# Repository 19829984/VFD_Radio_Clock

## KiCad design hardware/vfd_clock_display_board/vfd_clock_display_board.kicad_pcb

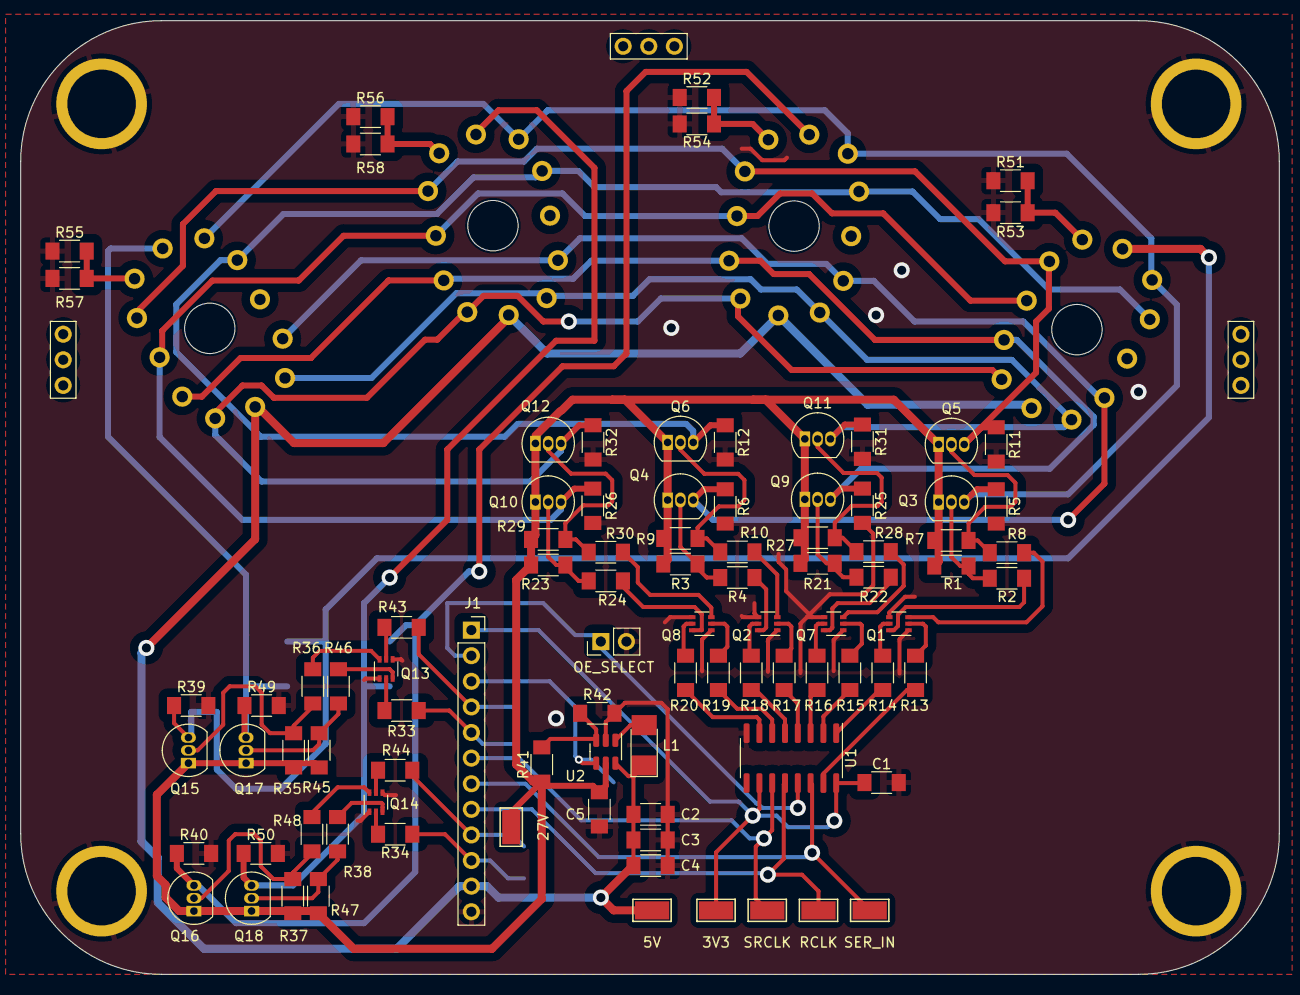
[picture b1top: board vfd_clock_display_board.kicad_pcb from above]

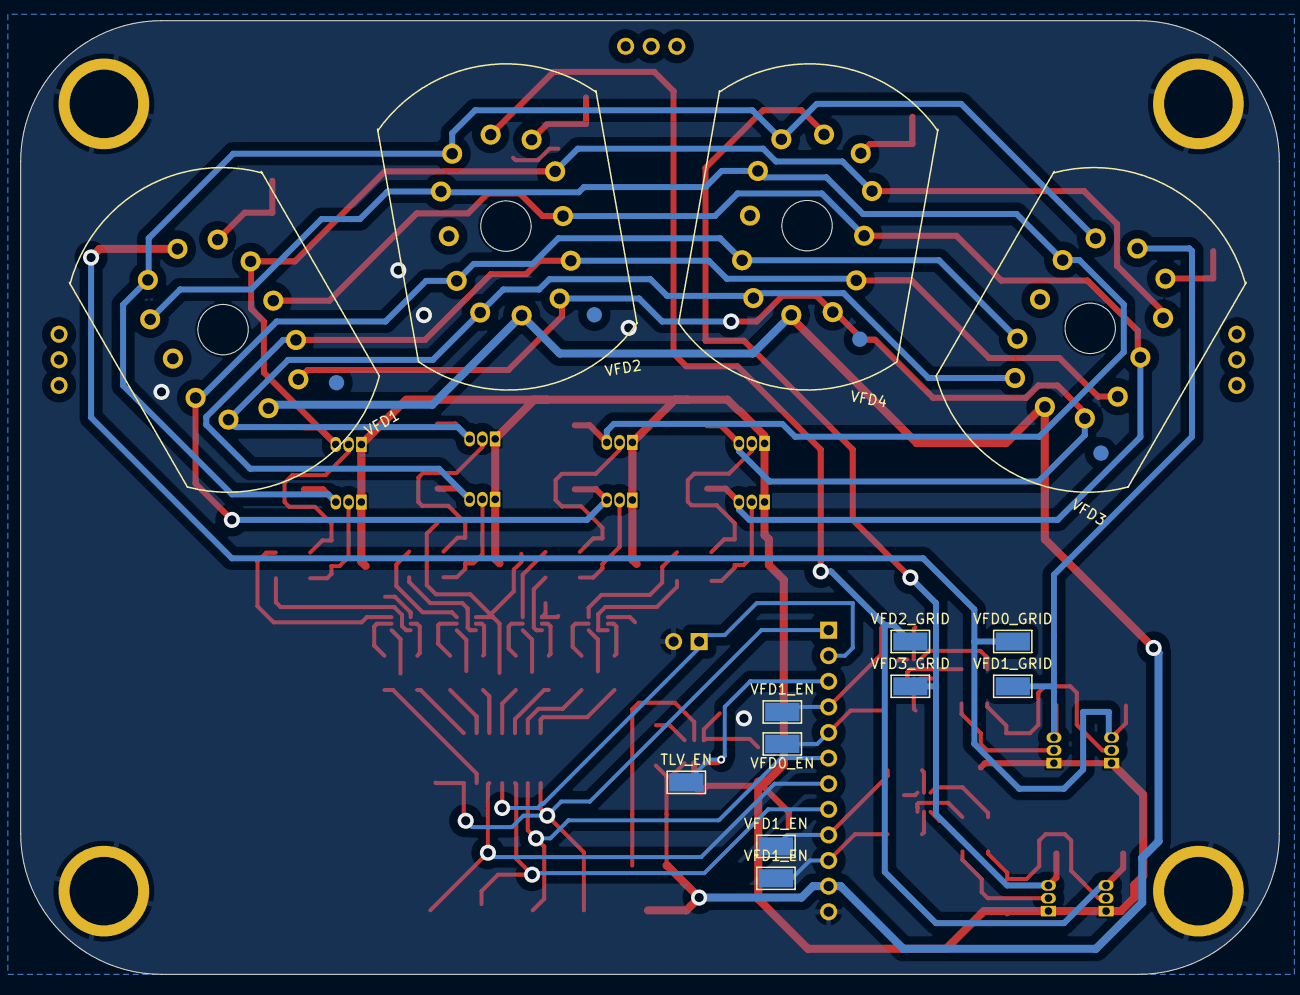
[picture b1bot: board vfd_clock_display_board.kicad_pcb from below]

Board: 2 copper layers, 124.9 x 94.6 mm, 105 parts (13 on the bottom side), 75 nets.

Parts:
3V3, 5V, 27V: TestPoint_Keystone_5015_Micro-Minature
C1, C2, C3, C4: 1uF; C_1206
C5: 10uF; C_1206
J1: Conn_01x12_Pin; PinSocket_1x12_P2.54mm_Vertical
L1: 22uH; L_1210
OE_SELECT: Conn_01x02_Pin; PinHeader_1x02_P2.54mm_Vertical
Q1, Q2, Q7, Q8, Q13, Q14: MMDT5551; SOT-363_SC-70-6
Q3, Q4, Q5, Q6, Q9, Q10, Q11, Q12, Q15, Q16, Q17, Q18: 2N3906; TO-92_Inline
R1, R3, R7, R9, R21, R23, R27, R29, R35, R37, R45, R47: R_220K; R_1206
R2, R4, R8, R10, R22, R24, R28, R30, R36, R38, R46, R48: R_50K; R_1206
R5, R6, R11, R12, R25, R26, R31, R32, R39, R40, R49, R50: R_100K; R_1206
R13, R14, R15, R16, R17, R18, R19, R20, R33, R34, R43, R44: R_22K; R_1206
R41: 2.37M; R_1206
R42: 71.5K; R_1206
R51, R52, R53, R54, R55, R56, R57, R58: 75; R_1206
RCLK: TestPoint_Keystone_5015_Micro-Minature
SER_IN: TestPoint_Keystone_5015_Micro-Minature
SRCLK: TestPoint_Keystone_5015_Micro-Minature
TLV_EN: TestPoint_Keystone_5015_Micro-Minature
U1: 74HC595; SOIC-16_3.9x9.9mm_P1.27mm
U2: TLV61046ADB; SOT-23-6
VFD0_EN, VFD0_GRID, VFD1_EN, VFD1_EN#2, VFD1_EN#3, VFD1_GRID, VFD2_GRID, VFD3_GRID: TestPoint_Keystone_5015_Micro-Minature
VFD1, VFD2, VFD3, VFD4: IV-22

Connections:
27V: 27V.1, C5.1, Q3.1 (E), Q4.1 (E), Q5.1 (E), Q6.1 (E), Q9.1 (E), Q10.1 (E), Q11.1 (E), Q12.1 (E), Q15.1 (E), Q16.1 (E), Q17.1 (E), Q18.1 (E), R1.1, R3.1, R7.1, R9.1, R21.1, R23.1, R27.1, R29.1, R35.1, R37.1, R41.1, R45.1, R47.1, U2.5 (VOUT)
/0QA: Q1.2 (B1), R13.1
/0QB: Q1.5 (B2), R14.1
/0QC: Q7.2 (B1), R15.2
/0QD: Q7.5 (B2), R16.2
/0QE: Q2.2 (B1), R17.2
/0QF: Q2.5 (B2), R18.1
/0QG: Q8.2 (B1), R19.1
/0QH: Q8.5 (B2), R20.1
/OE: J1.2, OE_SELECT.1, U1.13 (~OE)
/RCLK: J1.8, RCLK.1, U1.12 (RCLK)
/SER_IN: J1.7, SER_IN.1, U1.14 (SER)
/SRCLK: J1.6, SRCLK.1, U1.11 (SRCLK)
/TLV_EN: J1.3, TLV_EN.1, U2.4 (EN)
/VFD0_EN: J1.5, R33.2, VFD0_EN.1
/VFD0_GRID: Q15.3 (C), R39.1, VFD0_GRID.1, VFD1.6 (Grid)
/VFD1_EN: J1.4, R43.1, VFD1_EN.1
/VFD1_GRID: Q17.3 (C), R49.1, VFD1_GRID.1, VFD3.6 (Grid)
/VFD2_EN: J1.10, R34.1, VFD1_EN#3.1
/VFD2_GRID: Q16.3 (C), R40.1, VFD2.6 (Grid), VFD2_GRID.1
/VFD3_EN: J1.9, R44.1, VFD1_EN#2.1
/VFD3_GRID: Q18.3 (C), R50.1, VFD3_GRID.1, VFD4.6 (Grid)
/VFD_A: Q3.3 (C), R5.1, VFD1.7 (A), VFD2.7 (A), VFD3.7 (A), VFD4.7 (A)
/VFD_B: Q5.3 (C), R11.1, VFD1.4 (B), VFD2.4 (B), VFD3.4 (B), VFD4.4 (B)
/VFD_C: Q9.3 (C), R25.1, VFD1.2 (C), VFD2.2 (C), VFD3.2 (C), VFD4.2 (C)
/VFD_D: Q11.3 (C), R31.1, VFD1.11 (D), VFD2.11 (D), VFD3.11 (D), VFD4.11 (D)
/VFD_DP: Q12.3 (C), R32.1, VFD1.1 (DP), VFD2.1 (DP), VFD3.1 (DP), VFD4.1 (DP)
/VFD_E: Q4.3 (C), R6.1, VFD1.10 (E), VFD2.10 (E), VFD3.10 (E), VFD4.10 (E)
/VFD_F: Q6.3 (C), R12.1, VFD1.8 (F), VFD2.8 (F), VFD3.8 (F), VFD4.8 (F)
/VFD_G: Q10.3 (C), R26.1, VFD1.3 (G), VFD2.3 (G), VFD3.3 (G), VFD4.3 (G)
unnamed: Q1.6 (C1), R2.2
unnamed: Q1.3 (C2), R8.2
unnamed: Q2.6 (C1), R4.2
unnamed: Q2.3 (C2), R10.2
unnamed: Q3.2 (B), R1.2, R2.1
unnamed: Q4.2 (B), R3.2, R4.1
unnamed: Q5.2 (B), R7.2, R8.1
unnamed: Q6.2 (B), R9.2, R10.1
unnamed: Q7.6 (C1), R22.2
unnamed: Q7.3 (C2), R28.2
unnamed: Q8.6 (C1), R24.2
unnamed: Q8.3 (C2), R30.2
unnamed: Q9.2 (B), R21.2, R22.1
unnamed: Q10.2 (B), R23.2, R24.1
unnamed: Q11.2 (B), R27.2, R28.1
unnamed: Q12.2 (B), R29.2, R30.1
unnamed: Q13.2 (B1), R33.1
unnamed: Q13.6 (C1), R36.2
unnamed: Q13.5 (B2), R43.2
unnamed: Q13.3 (C2), R46.2
unnamed: Q14.2 (B1), R34.2
unnamed: Q14.6 (C1), R38.2
unnamed: Q14.5 (B2), R44.2
unnamed: Q14.3 (C2), R48.2
unnamed: Q15.2 (B), R35.2, R36.1
unnamed: Q16.2 (B), R37.2, R38.1
unnamed: Q17.2 (B), R45.2, R46.1
unnamed: Q18.2 (B), R47.2, R48.1
unnamed: R13.2, U1.15 (QA)
unnamed: R14.2, U1.1 (QB)
unnamed: R15.1, U1.2 (QC)
unnamed: R16.1, U1.3 (QD)
unnamed: R17.1, U1.4 (QE)
unnamed: R18.2, U1.5 (QF)
unnamed: R19.2, U1.6 (QG)
unnamed: R20.2, U1.7 (QH)
unnamed: R41.2, R42.1, U2.3 (FB)
unnamed: L1.2, U2.1 (SW)
unnamed: R51.2, R53.2, VFD1.5 (Fil-)
unnamed: R52.2, R54.2, VFD2.5 (Fil-)
unnamed: R55.2, R57.2, VFD3.5 (Fil-)
unnamed: R56.2, R58.2, VFD4.5 (Fil-)
PWR_3V3: 3V3.1, C1.1, J1.1, U1.10 (~SRCLR), U1.16 (VCC)
PWR_5V: 5V.1, C2.1, C3.1, C4.1, J1.11, L1.1, U2.6 (VI), VFD1.12 (Fil+), VFD2.12 (Fil+), VFD3.12 (Fil+), VFD4.12 (Fil+)
PWR_GND: C1.2, C2.2, C3.2, C4.2, C5.2, J1.12, OE_SELECT.2, Q1.1 (E1), Q1.4 (E2), Q2.1 (E1), Q2.4 (E2), Q7.1 (E1), Q7.4 (E2), Q8.1 (E1), Q8.4 (E2), Q13.1 (E1), Q13.4 (E2), Q14.1 (E1), Q14.4 (E2), R5.2, R6.2, R11.2, R12.2, R25.2, R26.2, R31.2, R32.2, R39.2, R40.2, R42.2, R49.2, R50.2, R51.1, R52.1, R53.1, R54.1, R55.1, R56.1, R57.1, R58.1, U1.8 (GND), U2.2 (GND)

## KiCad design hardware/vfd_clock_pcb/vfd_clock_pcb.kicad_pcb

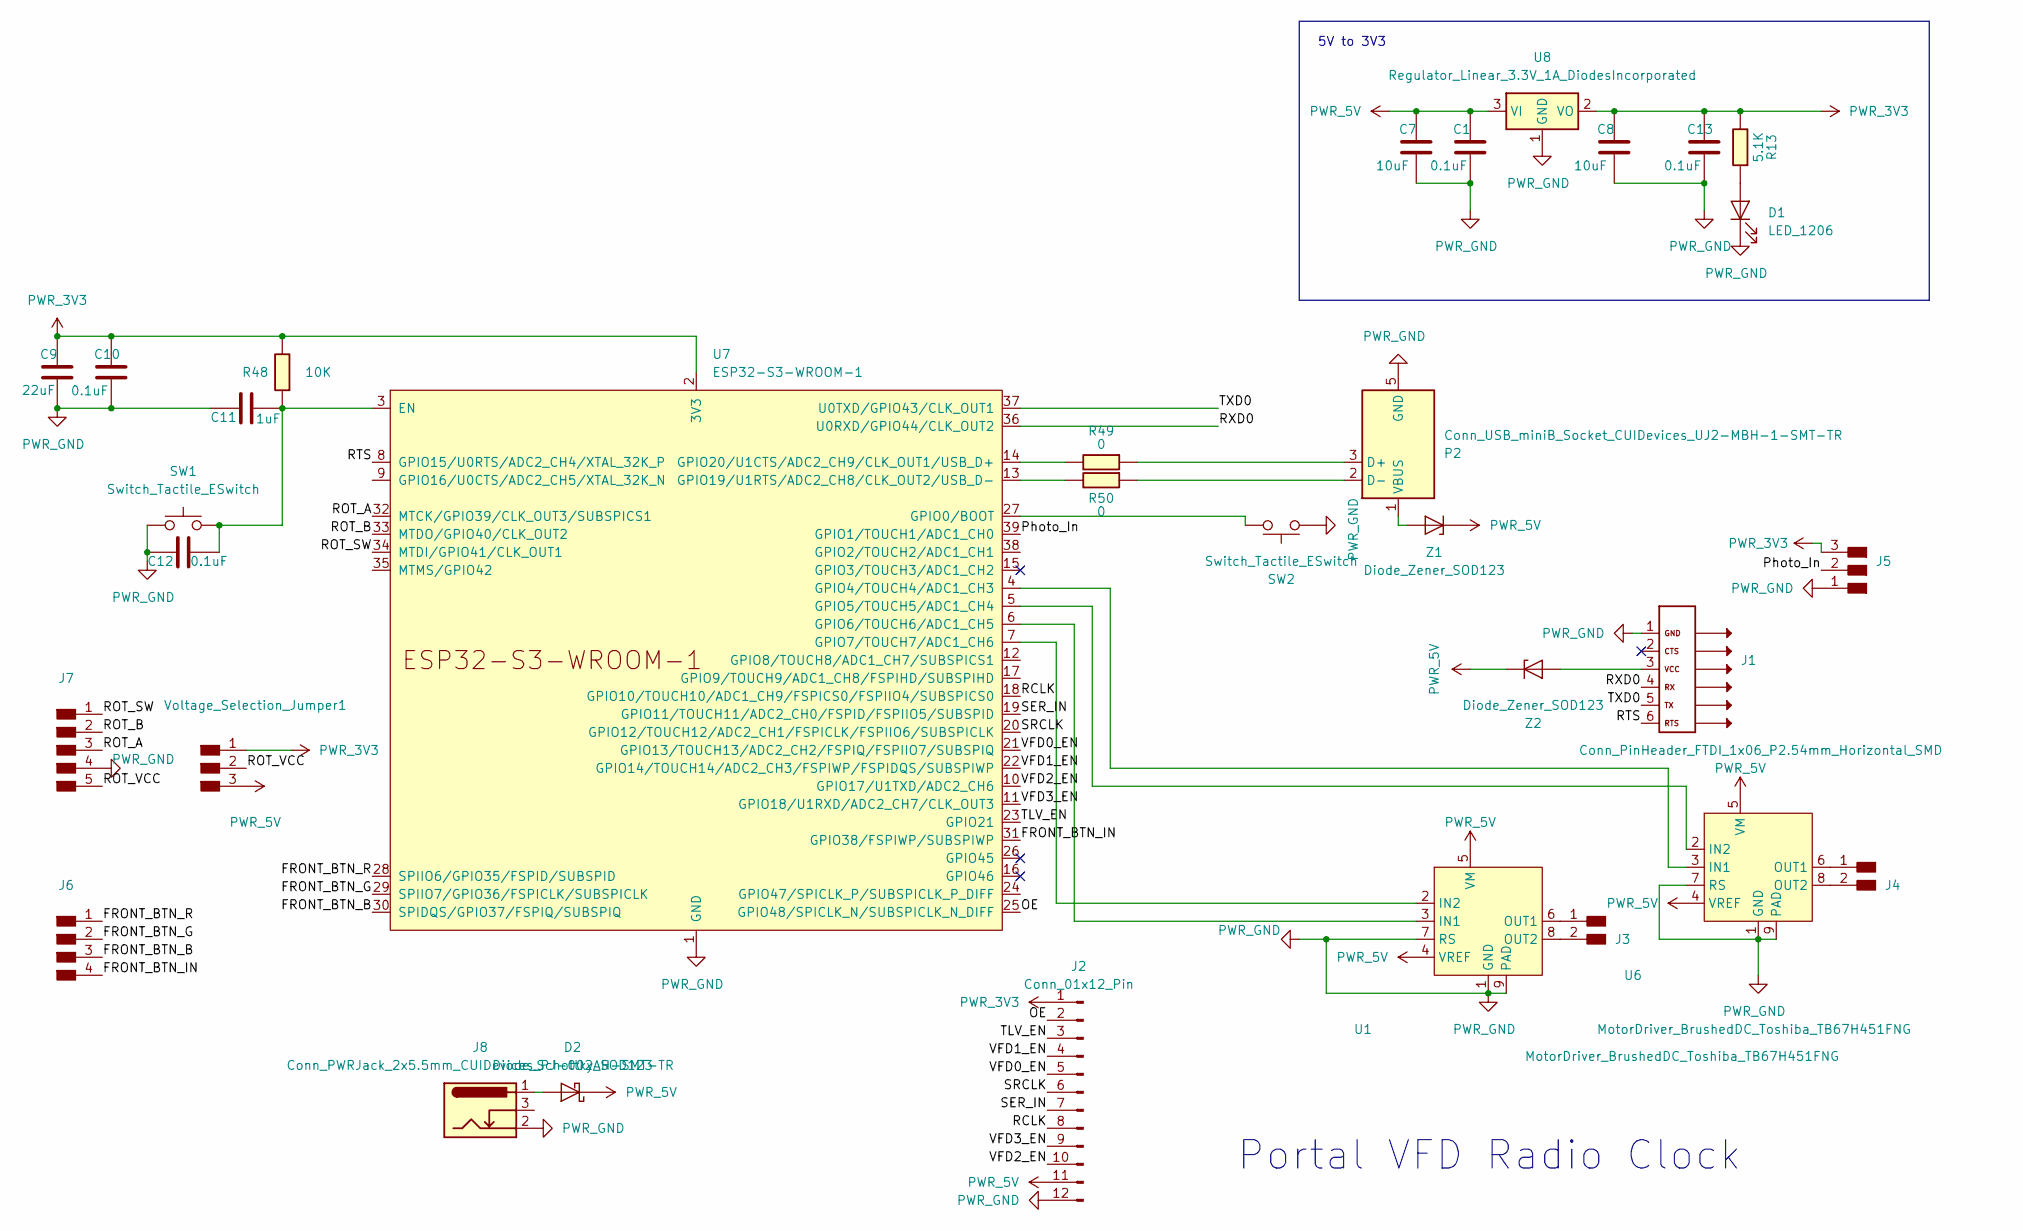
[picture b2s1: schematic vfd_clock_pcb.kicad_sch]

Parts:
C1, C10, C12, C13: 0.1uF; C_1206
C7, C8: 10uF; C_1206
C9: 22uF; C_1206
C11: 1uF; C_1206
D1: LED_1206
D2: Diode_Schottky_SOD123; SOD-123
J1: Conn_PinHeader_FTDI_1x06_P2.54mm_Horizontal_SMD; PinHeader_1x06_P2.54mm_Horizontal_SMD
J2: Conn_01x12_Pin; PinSocket_1x12_P2.54mm_Vertical
J3, J4: Conn_PinHeader_1x02_P2.54mm_Vertical_THT_D1mm; PinHeader_1x02_P2.54mm_Vertical_THT_D1mm
J5: Conn_PinHeader_1x03_P2.54mm_Vertical_THT_D1mm; PinHeader_1x03_P2.54mm_Vertical_THT_D1mm
J6: Conn_PinHeader_1x04_P2.54mm_Vertical_THT_D1mm; PinHeader_1x04_P2.54mm_Vertical_THT_D1mm
J7: Conn_PinHeader_1x05_P2.54mm_Vertical_THT_D1mm; PinHeader_1x05_P2.54mm_Vertical_THT_D1mm
J8: Conn_PWRJack_2x5.5mm_CUIDevices_PJ-002AH-SMT-TR; CUIDevices_PJ-002AH-SMT-TR_PWRJack_2x5.5mm
P2: Conn_USB_miniB_Socket_CUIDevices_UJ2-MBH-1-SMT-TR
R13: 5.1K; R_1206
R48: 10K; R_1206
R49, R50: 0; R_1206
SW1, SW2: Switch_Tactile_ESwitch; Button_ESwitch_TL3315NF100Q_4.5x4.5mm
U1, U6: MotorDriver_BrushedDC_Toshiba_TB67H451FNG; HSOP-8
U7: ESP32-S3-WROOM-1
U8: Regulator_Linear_3.3V_1A_DiodesIncorporated; SOT-223-3_TabPin2
Voltage_Selection_Jumper1: Conn_PinHeader_1x03_P2.54mm_Vertical_THT_D1mm; PinHeader_1x03_P2.54mm_Vertical_THT_D1mm
Z1, Z2: Diode_Zener_SOD123; SOD-123

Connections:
/FRONT_BTN_B: J6.3, U7.30 (SPIDQS/GPIO37/FSPIQ/SUBSPIQ)
/FRONT_BTN_G: J6.2, U7.29 (SPIIO7/GPIO36/FSPICLK/SUBSPICLK)
/FRONT_BTN_IN: J6.4, U7.31 (GPIO38/FSPIWP/SUBSPIWP)
/FRONT_BTN_R: J6.1, U7.28 (SPIIO6/GPIO35/FSPID/SUBSPID)
/OE: J2.2, U7.25 (GPIO48/SPICLK_N/SUBSPICLK_N_DIFF)
/Photo_In: J5.2, U7.39 (GPIO1/TOUCH1/ADC1_CH0)
/RCLK: J2.8, U7.18 (GPIO10/TOUCH10/ADC1_CH9/FSPICS0/FSPIIO4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)
/ROT_A: J7.3, U7.32 (MTCK/GPIO39/CLK_OUT3/SUBSPICS1)
/ROT_B: J7.2, U7.33 (MTDO/GPIO40/CLK_OUT2)
/ROT_SW: J7.1, U7.34 (MTDI/GPIO41/CLK_OUT1)
/ROT_VCC: J7.5, Voltage_Selection_Jumper1.2
/RTS: J1.6, U7.8 (GPIO15/U0RTS/ADC2_CH4/XTAL_32K_P)
/RXD0: J1.4, U7.36 (U0RXD/GPIO44/CLK_OUT2)
/SER_IN: J2.7, U7.19 (GPIO11/TOUCH11/ADC2_CH0/FSPID/FSPIIO5/S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)
/SRCLK: J2.6, U7.20 (GPIO12/TOUCH12/ADC2_CH1/FSPICLK/FSPIIO6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)
/TLV_EN: J2.3, U7.23 (GPIO21)
/TXD0: J1.5, U7.37 (U0TXD/GPIO43/CLK_OUT1)
/VFD0_EN: J2.5, U7.21 (GPIO13/TOUCH13/ADC2_CH2/FSPIQ/FSPIIO7/S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)
/VFD1_EN: J2.4, U7.22 (GPIO14/TOUCH14/ADC2_CH3/FSPIWP/FSPIDQS/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)
/VFD2_EN: J2.10, U7.10 (GPIO17/U1TXD/ADC2_CH6)
/VFD3_EN: J2.9, U7.11 (GPIO18/U1RXD/ADC2_CH7/CLK_OUT3)
unnamed: D1.2 (A), R13.2
unnamed: D2.2 (A), J8.1
unnamed: J3.1, U1.6 (OUT1)
unnamed: J3.2, U1.8 (OUT2)
unnamed: J4.1, U6.6 (OUT1)
unnamed: J4.2, U6.8 (OUT2)
unnamed: P2.3 (D+), R49.2
unnamed: P2.2 (D-), R50.2
unnamed: P2.1 (VBUS), Z1.2 (A)
unnamed: U1.3 (IN1), U7.6 (GPIO6/TOUCH6/ADC1_CH5)
unnamed: U1.2 (IN2), U7.7 (GPIO7/TOUCH7/ADC1_CH6)
unnamed: U6.3 (IN1), U7.4 (GPIO4/TOUCH4/ADC1_CH3)
unnamed: U6.2 (IN2), U7.5 (GPIO5/TOUCH5/ADC1_CH4)
unnamed: C11.2, C12.2, R48.2, SW1.3, SW1.4, U7.3 (EN)
unnamed: SW2.3, SW2.4, U7.27 (GPIO0/BOOT)
unnamed: R50.1, U7.13 (GPIO19/U1RTS/ADC2_CH8/CLK_OUT2/USB_D-)
unnamed: R49.1, U7.14 (GPIO20/U1CTS/ADC2_CH9/CLK_OUT1/USB_D+)
unnamed: J1.3, Z2.2 (A)
PWR_3V3: C8.1, C9.1, C10.1, C13.1, J2.1, J5.3, R13.1, R48.1, U7.2 (3V3), U8.2 (VO), Voltage_Selection_Jumper1.1
PWR_5V: C1.1, C7.1, D2.1 (K), J2.11, U1.4 (VREF), U1.5 (VM), U6.4 (VREF), U6.5 (VM), U8.3 (VI), Voltage_Selection_Jumper1.3, Z1.1 (K), Z2.1 (K)
PWR_GND: C1.2, C7.2, C8.2, C9.2, C10.2, C11.1, C12.1, C13.2, D1.1 (K), J1.1, J2.12, J5.1, J7.4, J8.2, P2.5 (GND), SW1.1, SW1.2, SW2.1, SW2.2, U1.1 (GND), U1.7 (RS), U1.9 (PAD), U6.1 (GND), U6.7 (RS), U6.9 (PAD), U7.1 (GND), U7.40 (GND), U7.41 (GND), U8.1 (GND)

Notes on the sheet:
5V to 3V3
Portal VFD Radio Clock

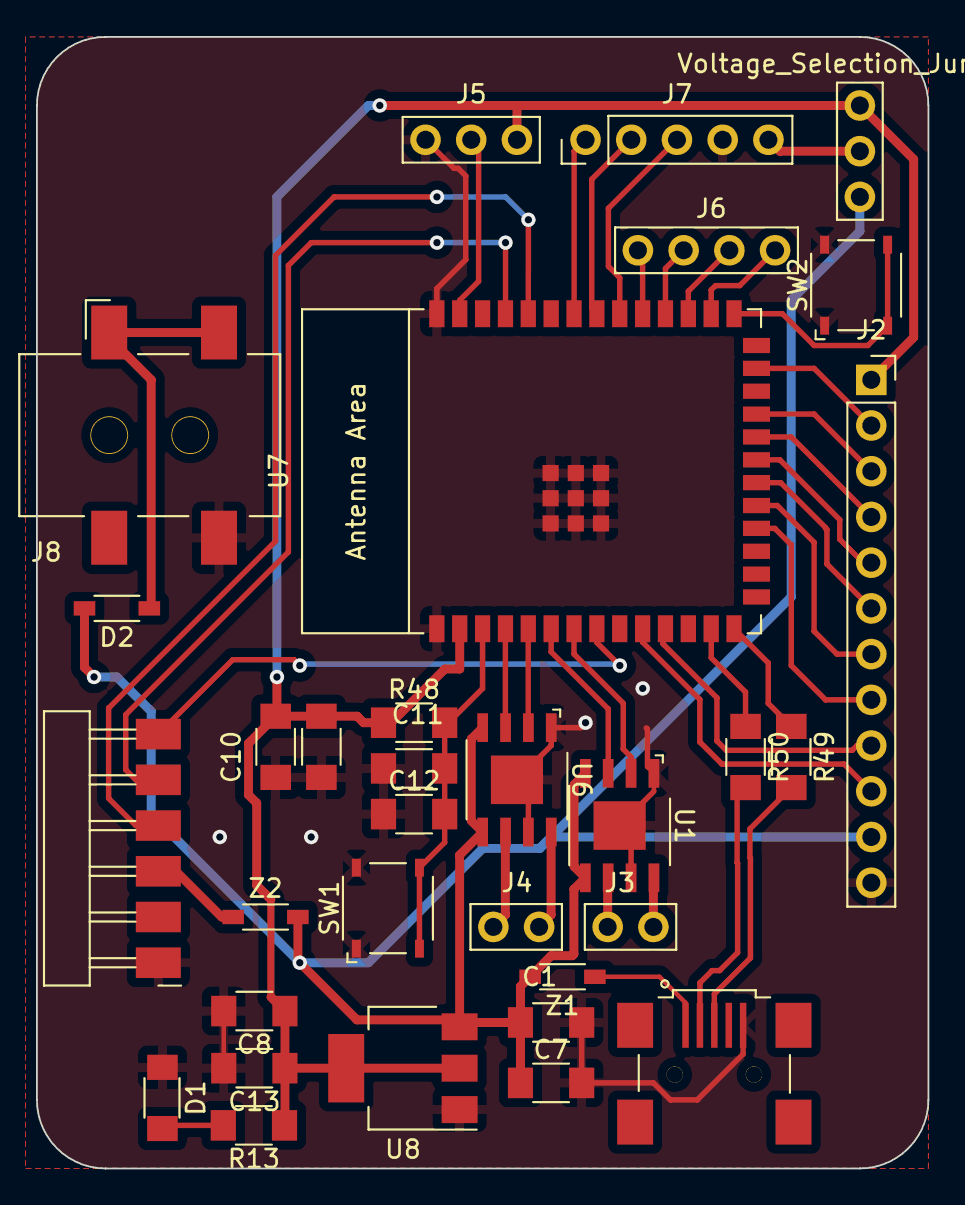
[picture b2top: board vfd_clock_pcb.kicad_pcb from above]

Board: 2 copper layers, 49.5 x 62.9 mm, 32 parts (0 on the bottom side), 42 nets.

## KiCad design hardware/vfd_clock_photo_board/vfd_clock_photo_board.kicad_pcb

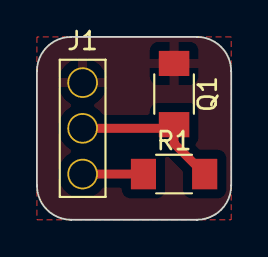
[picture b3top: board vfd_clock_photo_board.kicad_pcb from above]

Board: 2 copper layers, 10.8 x 10.2 mm, 3 parts (0 on the bottom side), 3 nets.

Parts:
J1: Conn_PinHeader_1x03_P2.54mm_Vertical_THT_D1mm; PinHeader_1x03_P2.54mm_Vertical_THT_D1mm
Q1: Phototransistor; Q_1206
R1: 10K; R_1206

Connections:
/Photo_Out: J1.2, Q1.2 (C), R1.2
PWR_3V3: J1.3, R1.1
PWR_GND: J1.1, Q1.1 (E)

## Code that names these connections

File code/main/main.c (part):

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
// GPIO
#define V27_EN_PIN 21
#define VFD0_EN_PIN 13
#define VFD1_EN_PIN 14
#define VFD2_EN_PIN 17
#define VFD3_EN_PIN 18
#define SHIFT_REG_OE_PIN 48
#define GPIO_OUTPUT_PIN_SEL ((1ULL << V27_EN_PIN) | (1ULL << SHIFT_REG_OE_PIN))

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// LEDC
#define LEDC_TIMER LEDC_TIMER_0
#define LEDC_MODE LEDC_LOW_SPEED_MODE
#define LEDC_HS_CH0_GPIO VFD0_EN_PIN
#define LEDC_HS_CH0_CHANNEL LEDC_CHANNEL_0
#define LEDC_HS_CH1_GPIO VFD1_EN_PIN
#define LEDC_HS_CH1_CHANNEL LEDC_CHANNEL_1
#define LEDC_HS_CH2_GPIO VFD2_EN_PIN
#define LEDC_HS_CH2_CHANNEL LEDC_CHANNEL_2
#define LEDC_HS_CH3_GPIO VFD3_EN_PIN
#define LEDC_HS_CH3_CHANNEL LEDC_CHANNEL_3
#define LEDC_DUTY_RES LEDC_TIMER_13_BIT // Set duty resolution to 13 bits
#define LEDC_DUTY (2048)                // Set duty to 50%. (2 ** 13) * 50% = 4096
#define LEDC_FREQUENCY (100)            // Frequency in Hertz. Set frequency at 100 Hz

uint8_t digit_index = 0;
uint8_t vfd_digits_io[4] = {VFD0_EN_PIN, VFD2_EN_PIN, VFD3_EN_PIN, VFD1_EN_PIN};
uint8_t digits_to_display[4] = {1, 2, 3, 4};
uint8_t decimal_point = 0b00000000;
spi_device_handle_t spi_handle = NULL;
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    // }

    // Dedicated GPIO
    const int bundleA_gpios[] = {VFD0_EN_PIN, VFD2_EN_PIN, VFD3_EN_PIN, VFD1_EN_PIN};
    gpio_config_t dedicated_io_conf = {
        .mode = GPIO_MODE_OUTPUT,
    };
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    gpio_set_level(V27_EN_PIN, 1);
    gpio_pulldown_en(SHIFT_REG_OE_PIN);
    gpio_set_level(SHIFT_REG_OE_PIN, 0);
    // gpio_set_level(VFD0_EN_PIN, 0);
    // gpio_set_level(VFD1_EN_PIN, 1);
    // gpio_set_level(VFD2_EN_PIN, 0);
    // gpio_set_level(VFD3_EN_PIN, 0);
    // gpio_dump_io_configuration();
    tx_data_test = 255;

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
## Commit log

2023-12-21 code update
2024-09-19 Add PCF version of main board, add test pads to display board
2024-10-04 start redesigning display board
2024-10-05 Further hardware redesign
2024-10-09 I forgor
2025-08-20 Somekind of hardware change, fix spi transaction
2025-08-25 Move main board code to its own folder, update display board to match latest
